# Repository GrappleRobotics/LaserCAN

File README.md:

# Grapple LaserCAN
Welcome to the open-source repository for the Grapple LaserCAN! That's right, everything's open source from the board files to the firmware.

**[Buy Here](https://grapplerobotics.au/)**

## [Looking for docs?](docs/getting-started.md)

## Project Directories
- [LaserCAN-Board](LaserCAN-Board) is the KiCAD project that contains the LaserCAN board files. 
- [lasercan-common](lasercan-common) are common libraries used between the firmware and bootloader.
- [lasercan-bootloader](lasercan-bootloader) is the CAN bootloader for the LaserCAN, written in Rust. The bootloader allows for over-the-air (or over-the-CAN, rather) firmware updates.
- [lasercan-firmware](lasercan-firmware) is the actual firmware for the LaserCAN, including sensor measurement and acquisition, CAN communication, and everything else it does!

## Loading your own firmware
If you want to load your own firmware onto the LaserCAN, clone this repository and make your changes to `lasercan-firmware`. You can flash this image to the board by running `python build.py firmware` and flashing the `target/lasercan-firmware-update-VERSION.grplfw` file using GrappleHook.
**NOTE: Be careful about what firmware you flash - custom firmware may brick the firmware update process if you don't have a ST-Link probe handy.**

## Flashing a new bootloader
If you for whatever reason need to flash a new bootloader, or if a custom firmware has crashed and the watchdog hasn't picked it up, you can flash a new bootloader and firmware by running `python build.py flash`. This requires an ST-Link v2 compatible probe and a TagConnect TC-2050-NL cable to connect to the debug pads on the bottom of the LaserCAN.

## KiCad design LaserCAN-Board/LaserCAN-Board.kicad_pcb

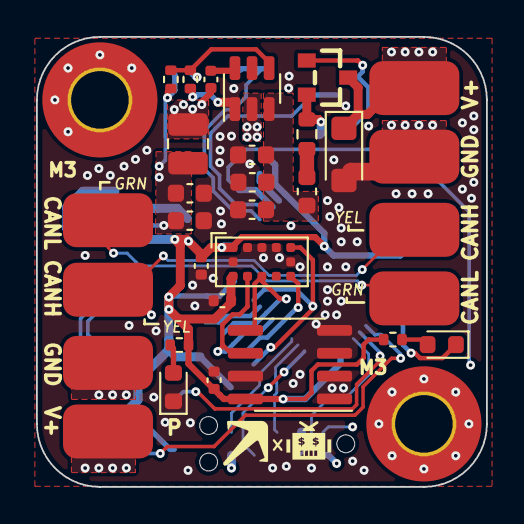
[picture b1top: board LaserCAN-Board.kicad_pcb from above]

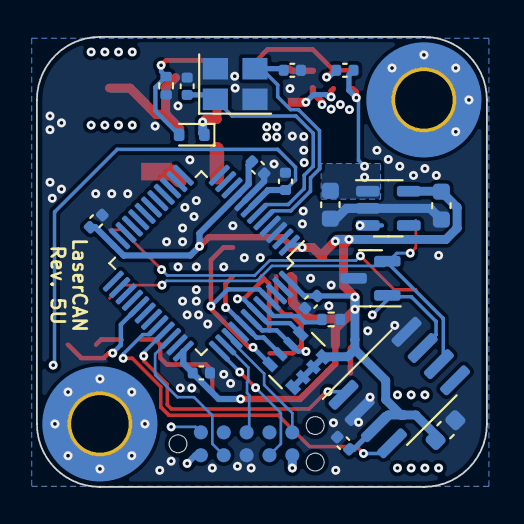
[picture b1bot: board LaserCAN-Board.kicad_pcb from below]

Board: 4 copper layers, 25.0 x 25.0 mm, 57 parts (22 on the bottom side), 32 nets.

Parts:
C1, C3, C12, C16, C17, C19: 10uF; C_0603_1608Metric
C2, C4, C5, C6, C7, C8, C9, C14, C15, C18: 100n; C_0402_1005Metric
C10, C11: 22uF; C_0603_1608Metric
C13: 33pF; C_0402_1005Metric
C20, C21: 20pF; C_0402_1005Metric
D1: 12V; D_SOD-523
D2: LED_ORANGE; LED_0603_1608Metric
D3: LED GREEN; LED_0603_1608Metric
D4: ESDCAN24-2BLY; SOT-23
D6: SMF15CA; D_SMF
FB1: BLM18AG102SN1D; L_0603_1608Metric
H1, H2: MountingHole; MountingHole_3.2mm_M3_Pad_TopBottom
J1, J3, J4, J5, J6, J7, J8, J9: Pad
J2: TC2050-IDC-NL; TAG-CONNECT_TC2050-IDC-NL
L2: 22uH; L_1008_2520Metric
NT1: NetTie_2; NetTie-2_SMD_Pad0.5mm
NT2: NetTie_2; NetTie-2_SMD_Pad2.0mm
Q1: Si2309CDS-T1-GE3; SOT-23_L2.9-W1.3-P1.90-LS2.4-BR
R1, R10: 10k; R_0402_1005Metric
R2: 100k; R_0402_1005Metric
R6, R7: 220; R_0402_1005Metric
R8: 18.2k; R_0402_1005Metric
R9: 4.7; R_0603_1608Metric
RN1: YC164-JR-074K7L; R_Array_Convex_4x0603
U1: TPS7A2033PDBVR; SOT-23-5
U2: VL53L1CXV0FY1; ST_VL53L1x
U3: M24C64-RMN6TP; SOIC-8_3.9x4.9mm_P1.27mm
U4: STM32F103C8Tx; LQFP-48_7x7mm_P0.5mm
U6: SN65HVD230; SOIC-8_3.9x4.9mm_P1.27mm
U9: TPS54202DDC; SOT-23-6
Y1: 8MHz 12pF; Crystal_SMD_3225-4Pin_3.2x2.5mm

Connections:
+3V3: C2.1, C3.1, C5.2, C6.1, C7.1, C8.1, C9.2, C14.1, C15.1, C19.1, J2.1, R6.1, R7.1, RN1.5 (R4.2), RN1.6 (R3.2), RN1.7 (R2.2), RN1.8 (R1.2), U1.5 (OUT), U2.1 (AVDDVCSEL), U2.11 (AVDD), U3.8 (VCC), U4.1 (VBAT), U4.9 (VDDA), U4.24 (VDD), U4.36 (VDD), U4.48 (VDD), U6.3 (VCC)
+12V: D6.1 (A1), J1.1, J2.5, J3.1, Q1.3 (D)
/3V87: C1.1, C10.1, C11.1, C13.1, L2.2, R2.1, U1.1 (IN), U1.3 (EN)
/BUCK_SW: C18.2, L2.1, U9.2 (SW)
/CANH: D4.1 (K), J8.1, J9.1, U6.7 (CANH)
/CANL: D4.2 (K), J6.1, J7.1, U6.6 (CANL)
/CAN_RX: U4.32 (PA11), U6.4 (R)
/CAN_TX: U4.33 (PA12), U6.1 (D)
/I2C_SCL: RN1.2 (R2.1), U2.10 (SCL), U3.6 (SCL), U4.42 (PB6)
/I2C_SDA: RN1.1 (R1.1), U2.9 (SDA), U3.5 (SDA), U4.43 (PB7)
/JTDI: J2.8, U4.38 (PA15)
/JTDO: J2.6, U4.39 (PB3)
/NRST: C4.2, J2.10, U4.7 (NRST)
/PWR_IN_FILT: C12.1, C16.1, C17.1, FB1.2, U9.3 (VIN)
/STATUS_LED: D2.1 (K), U4.29 (PA8)
/SWCLK/JTCK: J2.4, U4.37 (PA14)
/SWDIO/JTMS: J2.2, U4.34 (PA13)
/TOF_INT: RN1.3 (R3.1), U2.7 (GPIO1), U4.41 (PB5)
/TOF_SHUT: RN1.4 (R4.1), U2.5 (XSHUT), U4.45 (PB8)
GND: C1.2, C2.2, C3.2, C4.1, C5.1, C6.2, C7.2, C8.2, C9.1, C10.2, C11.2, C12.2, C14.2, C15.2, C16.2, C17.2, C19.2, C20.1, C21.1, D3.1 (K), D4.3 (A), D6.2 (A2), J2.3, NT1.2, NT2.1, R1.1, R10.1, U1.2 (GND), U2.2 (AVSSVCSEL), U2.3 (GND), U2.4 (GND), U2.6 (GND), U2.12 (GND), U3.1 (E0), U3.2 (E1), U3.3 (E2), U3.4 (VSS), U3.7 (~WC), U4.3 (PC14), U4.4 (PC15), U4.8 (VSSA), U4.23 (VSS), U4.35 (VSS), U4.47 (VSS), U6.2 (GND), U6.8 (Rs), U9.1 (GND), Y1.2, Y1.4
GNDPWR: J4.1, J5.1, NT2.2
unnamed: D1.2 (A), Q1.1 (G), R1.2
unnamed: D1.1 (K), Q1.2 (S), R9.1
unnamed: D2.2 (A), R6.2
unnamed: D3.2 (A), R7.2
unnamed: FB1.1, R9.2
unnamed: NT1.1, R8.2
unnamed: R10.2, U4.44 (BOOT0)
unnamed: C21.2, U4.5 (PD0), Y1.3
unnamed: C20.2, U4.6 (PD1), Y1.1
unnamed: C18.1, U9.6 (BOOT)
unnamed: C13.2, R2.2, R8.1, U9.4 (FB)

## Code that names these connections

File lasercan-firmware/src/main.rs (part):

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    let mut gpioc = ctx.device.GPIOC.split();
    let mut afio = ctx.device.AFIO.constrain();

    let pc15_board_rev_detect = gpioc.pc15.into_pull_up_input(&mut gpioc.crh);
    let pc14_board_rev_detect = gpioc.pc14.into_pull_up_input(&mut gpioc.crh);
    
    let mut flash = ctx.device.FLASH.constrain();

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
    feed_watchdog(&mut ctx.device.IWDG);

    let mut tof_shut_pin = match pc14_board_rev_detect.is_low() {
      false => {
        // Rev 4 or earlier
        let (_pa15, _pb3, pb4) = afio.mapr.disable_jtag(gpioa.pa15, gpiob.pb3, gpiob.pb4);
        pb4.into_push_pull_output(&mut gpiob.crl).erase()
      },
      true => {
        // Rev 5 or later
        gpiob.pb8.into_push_pull_output(&mut gpiob.crh).erase()
      }
    };
    tof_shut_pin.set_low();

    /* TIMER INIT */
    let mut systick = ctx.core.SYST.counter_us(&clocks);
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
    /* LED INIT */

    let mut status_led = gpioa.pa8.into_push_pull_output(&mut gpioa.crh);
    status_led.set_low();

    let mut led_timer = ctx.device.TIM1.counter_ms(&clocks);
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    heap_init();

    /* I2C INIT */
    let scl = gpiob.pb6.into_alternate_open_drain(&mut gpiob.crl);
    let sda = gpiob.pb7.into_alternate_open_drain(&mut gpiob.crl);
    let i2c = BlockingI2c::i2c1(
      ctx.device.I2C1,
      (scl, sda),
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    );
    
    // This is ugly, but what can you do?
    let i2c_bus = new_cortexm!(BlockingI2c<I2C1, ( stm32f1xx_hal::gpio::gpiob::PB6<Alternate<OpenDrain>>, stm32f1xx_hal::gpio::gpiob::PB7<Alternate<OpenDrain>> )> = i2c).unwrap();
    
    /* CAN INIT */
    
    let can = Can::new(ctx.device.CAN1, ctx.device.USB);
    let rx = gpioa.pa11.into_floating_input(&mut gpioa.crh);
    let tx = gpioa.pa12.into_alternate_push_pull(&mut gpioa.crh);
    
    can.assign_pins((tx, rx), &mut afio.mapr);
    
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    /* SENSOR INIT */
    let mut delay = ctx.device.TIM4.delay_ms(&clocks);

    tof_shut_pin.set_high();  // Enable sensor (shutdown is active low)
    
    // Give the sensor some time to start up
    delay.delay_ms(20u16);
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
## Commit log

2023-03-28 Initial LaserCAN commit
2023-03-28 Implement LaserCAN - now working with RoboRIO
2023-03-29 First LaserCAN firmware release
2023-03-29 Update version to be the LaserCAN revision
2023-12-16 Initial LaserCAN commit
    Implement LaserCAN - now working with RoboRIO
    First LaserCAN firmware release
    Update version to be the LaserCAN revision
    Remove firmware, put it elsewhere
    V2 Initial Design
    Add new layout
2023-12-16 Update LICENSE
2023-12-16 Add buy here link
2023-12-16 Update getting started guide to be transparent about power supply limits
2023-12-16 Update power supply note again
2023-12-16 Add major dimensions
2023-12-16 Update examples
2023-12-16 Update to match new namespace
2023-12-17 Update getting started
2023-12-17 Add PDF Schematic
2023-12-17 Add STEP file
2023-12-18 Update examples to be for 2024
2023-12-18 Update to v3.1 - Improved voltage regulation performance, improved ESD protection
2023-12-19 Update to new power regulation circuitry
2023-12-20 Add new power regulation, completely re-route board to accomodate
2023-12-20 Add new schematic
2023-12-20 Add LED feedback based on distance to target
2023-12-20 Remove errant .zip file
2023-12-20 Modify the routing a little bit
2023-12-20 Add a Transparent Rev4 LaserCAN
2023-12-21 Update getting started guide, update firmware to be tolerant to large queues
2023-12-21 Rev 4 updates
2023-12-21 Rev 4 - more updates
2023-12-21 Rev 4 Complete, barring any more review
2023-12-22 Rev 4 updates - NPTH, improved routing, BOM optimisation
2023-12-22 Slight part number change
2023-12-25 Update to 2024, add replies for requests
2023-12-25 Add check for bootloader compat, update bootloader, update firmware
2023-12-25 Update CI
2023-12-25 Add apt packages
2023-12-25 Helps if you use the correct package
2023-12-25 Add nop patch to fix bootloader compat
2023-12-25 Add nops to avoid firmware flashing issues
2023-12-26 Update to python build script
2023-12-26 Try this
2023-12-26 CI debugging
2023-12-26 Try using Popen instead
2023-12-26 Include nop again
2023-12-26 Add release if applicable
2023-12-26 Update frc-msgs to be more slim
2023-12-26 Bump version
2024-01-04 Initial move to a unified impl
2024-01-04 Things appear to be mostly working, with the exception of some ACKs
2024-01-05 Use new associated lifetimes
2024-01-06 Fix blink, add getting started guide for Batch 2+
2024-01-06 Add Rev4 STEP file
2024-01-18 Start working on Rev5
2024-01-18 Rev 5 Updates
2024-01-21 Slight changes
2024-01-21 Update to new libgrapplefrc version, add metadata to lasercan-impl
2024-01-21 Add extra match for when compiled with NI enabled
2024-01-26 Update getting started guide
2024-02-01 Updates for Rev 5
2024-04-01 Update to support new grplbndl flash method
2024-04-09 Clarify Star + Passthru
2024-06-19 Update build script to reflect connect-under-reset requirement for LaserCAN
2025-02-20 Update for configuration persistence
2026-03-18 Bootloader v2 updates
